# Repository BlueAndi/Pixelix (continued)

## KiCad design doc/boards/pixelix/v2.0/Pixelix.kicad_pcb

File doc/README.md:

# PIXELIX <!-- omit in toc -->

## Documentation  <!-- omit in toc -->

- [Hardware](#hardware)
- [Software](#software)
- [Issues, Ideas And Bugs](#issues-ideas-and-bugs)
- [License](#license)
- [Contribution](#contribution)

## Hardware

- [Boards](./boards/README.md)
- [Sensors](SENSORS.md)

## Software

- [Software architecture](./architecture/README.md)
- [CI and release workflows](WORKFLOWS.md)
- [Software configuration management](./config/README.md)
  - [Toolchain installation](./config/TOOLCHAIN-INSTALLATION.md)
  - [Software build](./config/SW-BUILD.md)
  - [Software update](./config/SW-UPDATE.md)
- [Plugins](PLUGINS.md)
- [Plugin Development](PLUGIN-DEV.md)
- [Websocket API description](WEBSOCKET.md)
- [Coredump Analysis & Debugging](COREDUMP-ANALYSIS.md)
- [Alternative icons](ICONS.md)
- [Configuration examples for GrabViaMqttPlugin and GrabViaRestPlugin.](./grabConfigs/README.md)

## Issues, Ideas And Bugs

If you have ideas or found a bug, create an [issue](https://github.com/BlueAndi/Pixelix/issues). If you want to fix it yourself, clone the repository and open a pull request.

## License

The whole source code is published under the [MIT license](http://choosealicense.com/licenses/mit/).
Consider the different licenses of the used third party libraries too!

## Contribution

Unless you explicitly state otherwise, any contribution intentionally submitted for inclusion in the work by you, shall be licensed as above, without any
additional terms or conditions.

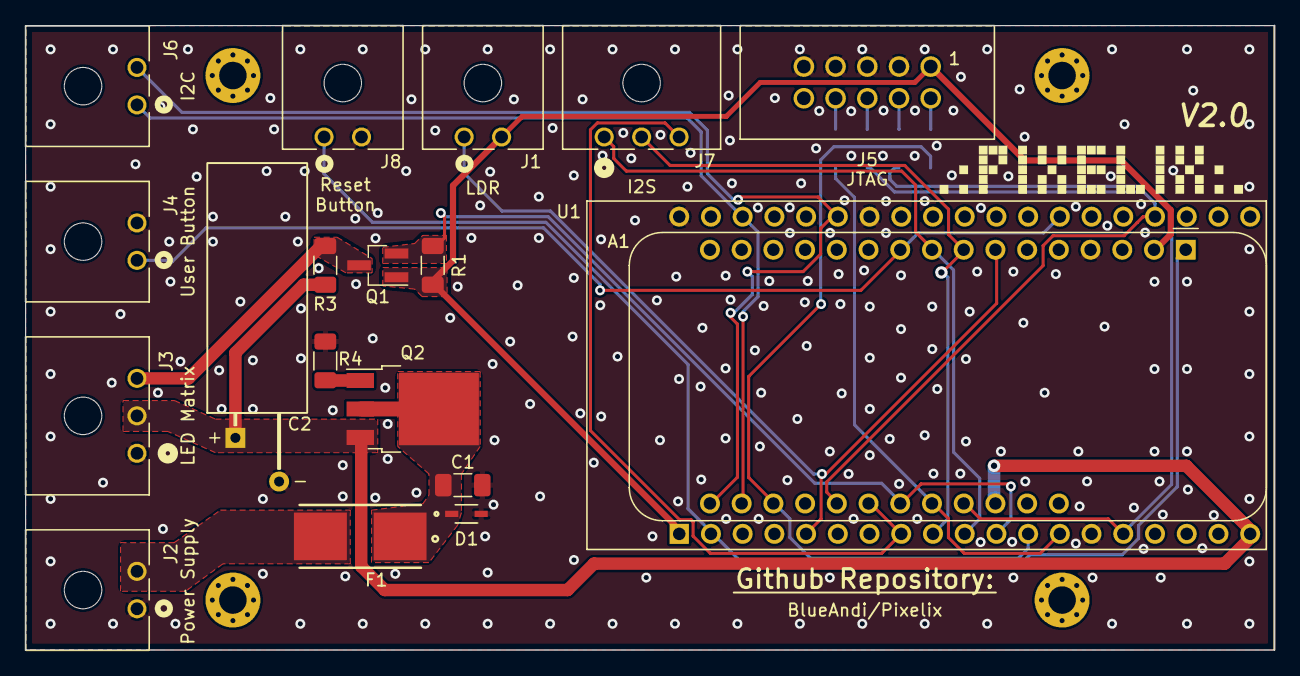
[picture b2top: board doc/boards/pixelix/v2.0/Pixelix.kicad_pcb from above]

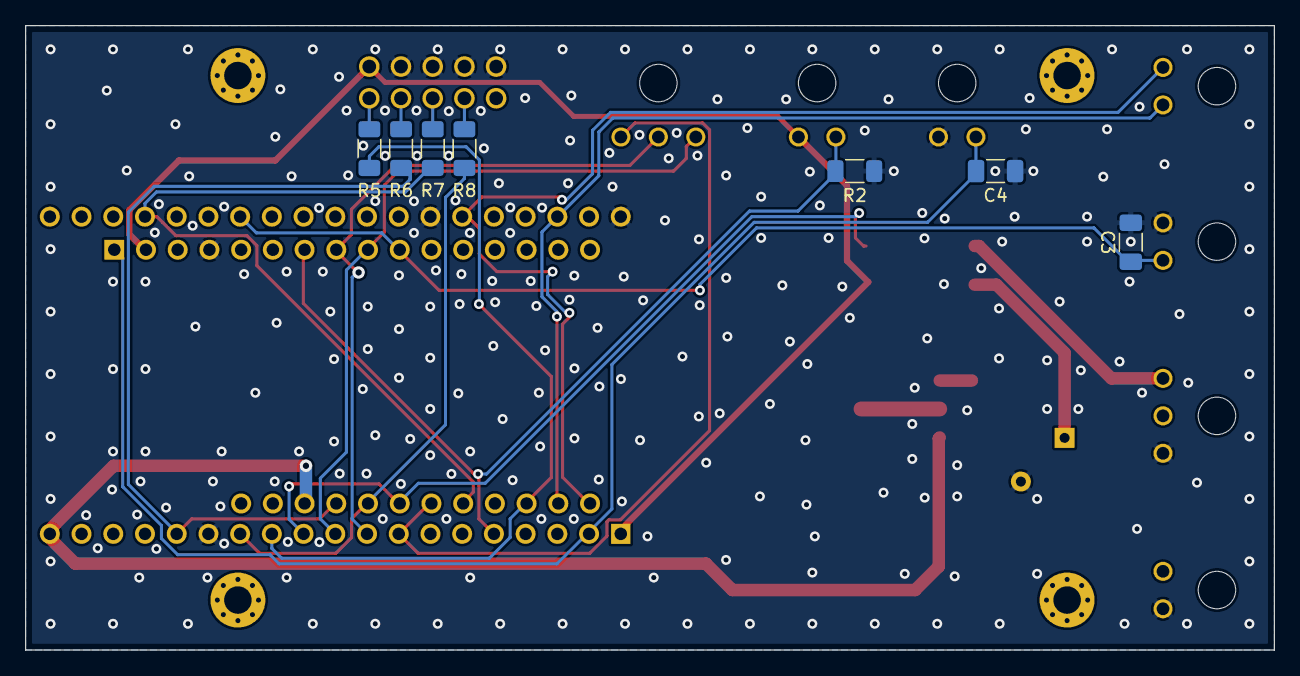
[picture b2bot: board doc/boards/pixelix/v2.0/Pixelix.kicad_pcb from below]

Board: 2 copper layers, 100.0 x 50.0 mm, 30 parts (7 on the bottom side), 24 nets.

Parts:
A1: Adafruit_Feather_V2_ESP32
C1, C3, C4: 100n; C_1206_3216Metric_Pad1.33x1.80mm_HandSolder
C2: 1000u / 16V; CP_Radial_D8.0mm_P3.50mm_horizontal
D1: CDSOD323-T05C
F1: 4A; FUSE_0154004.DR
H1, H2, H3, H4: MountingHole_Pad; MountingHole_2.2mm_M2_Pad_Via
J1, J2, J4, J6, J8: Conn_01x02; 66200211022
J3, J7: Conn_01x03; 66200311022
J5: Conn_02x05_Odd_Even; 61201021621
Q1: NMOS_GSD_BSS138; SOT-23_Handsoldering
Q2: PMOS_GDS_STD26P3LLH6; TO-252-3_TabPin2
R1: 10k; R_1206_3216Metric_Pad1.30x1.75mm_HandSolder
R2: 1k; R_1206_3216Metric_Pad1.30x1.75mm_HandSolder
R3: 1.2k; R_1206_3216Metric_Pad1.30x1.75mm_HandSolder
R4: 100k; R_1206_3216Metric_Pad1.30x1.75mm_HandSolder
R5, R6, R7, R8: 100; R_1206_3216Metric_Pad1.30x1.75mm_HandSolder
U1: ESP32-DEVKITC-32D; MODULE_ESP32-DEVKITC-32D

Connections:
+3V3: A1.2 (3V3), J1.2, J5.1, Q1.1 (G), R1.1, U1.1 (3V3)
/HV-DATA-OUT: J3.3, Q1.3 (D), R3.2
/I2S_CLK: A1.9 (IO36/A4), J7.1, U1.10 (IO26)
/I2S_Data_IN: A1.22 (A9/IO33), J7.3, U1.8 (IO33)
/I2S_WS: A1.8 (I39/A3), J7.2, U1.9 (IO25)
/LDR-ANALOG-IN: A1.7 (I34/A2), J1.1, R2.1, U1.5 (IO34)
/LV-DATA-OUT: A1.23 (A10/IO27), Q1.2 (S), R1.2, U1.11 (IO27)
/MTCK: A1.25 (A12/IO13), R6.2, U1.15 (IO13)
/MTDI: A1.24 (A11/IO12), R8.2, U1.13 (IO12)
/MTDO: A1.21 (A8/IO15), R7.2, U1.35 (IO15)
/MTMS: A1.19 (A6/IO14), R5.2, U1.12 (IO14)
/RESET: A1.1 (~RESET), C4.1, J8.1, U1.2 (EN)
/SCL: A1.18 (SCL/IO22), J6.1, U1.22 (IO22)
/SDA: A1.17 (SDA/IO23), J6.2, U1.25 (IO21)
/USER-BUTTON: A1.10 (IO4/A5), C3.1, J4.1, U1.32 (IO4)
/VCC-PROTECTED: A1.26 (USB), C2.1, J3.2, Q2.3 (S), R3.1, U1.19 (EXT_5V)
GND: A1.4 (GND), C1.2, C2.2, C3.2, C4.2, D1.2, J2.1, J3.1, J4.2, J5.3, J5.5, J5.7, J5.9, J8.2, R2.2, R4.2, U1.14 (GND1), U1.20 (GND3), U1.26 (GND2)
unnamed: C1.1, D1.1, F1.1, Q2.2 (D)
unnamed: F1.2, J2.2
unnamed: J5.2, R5.1
unnamed: J5.4, R6.1
unnamed: J5.6, R7.1
unnamed: J5.8, R8.1
unnamed: Q2.1 (G), R4.1

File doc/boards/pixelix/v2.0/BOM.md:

# PIXELIX
![PIXELIX](../../../images/LogoBlack.png)

[![License](https://img.shields.io/badge/license-MIT-blue.svg)](http://c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

# BOM

| Amount | Description | Package | Part | URL |
| --- | --- | --- | --- | --- |
| 1 | Adafruit Feather V2 | Feather V2 | A1 | [Adafruit](https://www.adafruit.com/product/5400), [Amazon](https://www.amazon.de/-/en/Adafruit-ESP32-Feather-V2-8MB-Fla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, [Mouser](https://www.mouser.de/ProductDetail/Adafruit/5400?qs=MyNHzdo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 |
| 3 | Capacitor 100 nF | C1206 | C1, C3, C4 | [Reichelt](https://www.reichelt.de/vielschicht-kerko-100nf-50v-125-c-ke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, [Mouser](https://www.mouser.de/ProductDetail/KEMET/C1206C104K5RACTM?q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 |
| 1 | Capacitor 1000 uF / 16 V | E5-8.5 | C2 | [Reichelt](https://www.reichelt.de/elko-radial-1-0-mf-16-v-105-c-low-es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, [Mouser](https://www.mouser.de/ProductDetail/Panasonic/EEU-FR1C102L?q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 |
| 4 | Resistor 100 Ohm | R1206 | R5, R6, R7, R8 | [Reichelt](https://www.reichelt.de/smd-widerstand-1206-100-ohm-250-mw-5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, [Mouser](https://www.mouser.de/ProductDetail/YAGEO/RC1206JR-07100RL?q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 |
| 1 | Resistor 1 kOhm | R1206 | R2 | [Reichelt](https://www.reichelt.de/smd-widerstand-1206-1-0-kohm-250-mw-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, [Mouser](https://www.mouser.de/ProductDetail/YAGEO/RC1206JR-071KL?qs=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  |
| 1 | Resistor 1.2 kOhm | R1206 | R3 | [Reichelt](https://www.reichelt.de/smd-widerstand-1206-1-2-kohm-250-mw-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, [Mouser](https://www.mouser.de/ProductDetail/YAGEO/RC1206JR-071K2L?qs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  |
| 1 | Resistor 10 kOhm | R1206 | R1 | [Reichelt](https://www.reichelt.de/smd-widerstand-1206-10-kohm-250-mw-5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, [Mouser](https://www.mouser.de/ProductDetail/YAGEO/RC1206JR-0710KL?qs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 |
| 1 | Resistor 100 kOhm | R1206 | R4 | [Reichelt](https://www.reichelt.de/smd-widerstand-1206-100-kohm-250-mw-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, [Mouser](https://www.mouser.de/ProductDetail/YAGEO/RC1206FR-07100KL?q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 |
| 1 | ESD suppressor CDSOD323-T05C | SOD-323 | D1 | [Conrad](https://www.conrad.de/de/p/bourns-tvs-diode-cdsod323-t05c-so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, [Farnell](https://de.farnell.com/bourns/cdsod323-t05c/tvs-diode-bidir-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, [Mouser](https://www.mouser.de/ProductDetail/Bourns/CDSOD323-T05C?qs=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 |
| 1 | Micro fuse block, 4A slow | OMNI-BLOK | F1 | [Reichelt](https://www.reichelt.de/smd-sicherungshalter-mit-sicherung-4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, [Farnell](https://de.farnell.com/littelfuse/0154004-drt/sicherung-smd-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, [Mouser](https://www.mouser.de/ProductDetail/?qs=gu7KAQ731UQeedYeniUN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 |
| 1 | Espressif ESP32-DEVKIT | ESP32-DEVKITC-32D | U1 | [Mouser](https://www.mouser.de/ProductDetail/Espressif-Systems/ESP32-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, [Amazon](https://www.amazon.de/s?k=ESP32-DEVKITC-32D&i=computers&__mk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 |
| 1 | N-channel mosfet BSS138 | SOT23 | Q1 | [Reichelt](https://www.reichelt.de/mosfet-n-ch-50v-0-22a-0-36w-sot-23-b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, [Farnell](https://de.farnell.com/on-semiconductor/bss138/mosfet-n-kana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, [Mouser](https://www.mouser.de/ProductDetail/onsemi-Fairchild/BSS138?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 |
| 1 | P-channel mosfet STD26P3LLH6 | TO252 | Q2 | [Reichelt](https://www.reichelt.de/mosfet-p-ch-30v-12a-0-03r-to252-std2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, [Farnell](https://de.farnell.com/stmicroelectronics/std26p3llh6/mosfet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, [Mouser](https://www.mouser.de/ProductDetail/STMicroelectronics/STD26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 |
| 5 | Conn_01x02 | Wuerth Elektronik 66200211022 | J1, J2, J4, J6, J8 | [Farnell](https://de.farnell.com/wurth-elektronik/66200211022/steckv-s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, [Mouser](https://www.mouser.de/c/?q=66200211022) |
| 2 | Conn_01x03 | Wuerth Elektronik 66200311022 | J3, J7 | [Farnell](https://de.farnell.com/wurth-elektronik/66200311022/stiftlei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, [Mouser](https://www.mouser.de/ProductDetail/Wurth-Elektronik/6620031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 |
| 1 | Conn_02x05_Odd_Even | Wuerth Elektronik 61201021621 | J5 | [Farnell](https://de.farnell.com/wurth-elektronik/61201021621/stiftlei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, [Mouser](https://www.mouser.de/ProductDetail/Wurth-Elektronik/6120102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 |
| --- | --- | --- | --- | --- |
| 5 | Plug_01x02 | Wuerth Elektronik 662002013322 | J1*, J2*, J4*, J6*, J8* | [Mouser](https://www.mouser.de/ProductDetail/Wurth-Elektronik/6620020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 |
| 2 | Plug_01x03 | Wuerth Elektronik 662003013322 | J3*, J7* | [Mouser](https://www.mouser.de/ProductDetail/Wurth-Elektronik/6620030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 |
| 1 | WS2812B 5050 8x32 RGB Flexible LED Panel Matrix | - | - | [Amazon](https://www.amazon.de/CHINLY-Flexible-Individuellement-adres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 |
| 1 | Power supply 5 V / 5 A (4 A would be enough) | - | - | [Reichelt](https://www.reichelt.de/tischnetzteil-25-w-5-v-5-a-mw-gst40a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, [Mouser](https://www.mouser.de/ProductDetail/CUI-Inc/SDM36-5-U-P5?qs=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 |
| 1 | Power cable | - | - | [Reichelt](https://www.reichelt.de/netzkabel-schutzkontaktstecker-gew-1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, [Mouser](https://www.mouser.de/ProductDetail/Qualtek/364002-D01?qs=HF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 |
| 1 | Power supply plug | - | - | [Mouser](https://www.mouser.de/ProductDetail/CUI-Devices/PJ-065A?qs=W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 |
| 1 | USER-Button | - | - | [Amazon](https://www.amazon.de/-/en/gp/product/B08L49F7DV) |
| 1 | RESET-Button | - | - | [Amazon](https://www.amazon.de/-/en/gp/product/B08YMZGLWX) |
| 1 | Light Sensor  | LDR5528  | - | [Amazon](https://www.amazon.de/-/en/AZDelivery-pieces-resistor-diodes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 |
| 1 | Audio Sensor-Module | INMP441  | - | [Amazon](https://www.amazon.de/-/en/gp/product/B09JFDJ9BF) |
| 4 | Insert-Nuts M2 | - | - | [Amazon](https://www.amazon.de/ruthex-Gewindeeinsatz-St%C3%BCck-Gewin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

* Note, only **ONE** ESP32 is required. Either U1 or A1.
* Note, you can also use the *Molex 2157601002* connectors for J1, J2, J4, J6 and J8 and the *Molex 2157601003* for J3 and J7.
* Note, you can also use the *Molex 2157591002* plugs for J1*, J2*, J4*, J6* and J8* and the *Molex 2157591003* for J3* and J7*. You also need crimp terminals (e.g. *Wuerth Elektronik 66200113722DEC* or *Molex 2064600021*)
* Do **NOT** combine connectors and plugs from Molex and Wuerth Elektronik!

# Issues, Ideas And Bugs
If you have further ideas or you found some bugs, great! Create a [issue](https://github.com/BlueAndi/esp-rgb-led-matrix/issues) or if you are able and willing to fix it by yourself, clone the repository and create a pull request.

# License
The whole source code is published under the [MIT license](http://choosealicense.com/licenses/mit/).

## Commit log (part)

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2026-06-03 Parse URL params into JSON and pass to plugins for advanced web config (ChicagoBusTrackerPlugin)
2026-06-08 Use proper formatting
2026-06-08 Make getApiKey private and const
2026-06-08 Fixup ChicagoBusTracker doxygen comments
2026-06-08 Explicit else cases in ChicagoBusTrackerPlugin::getTopic
2026-06-08 Refactor ChicagoBusTrackerPlugin::getApiKey to use JsonFile
2026-06-08 Explicit operator precedence in ChicagoBusTracker comparisons
2026-06-09 Bugfix: m_scrollCtrl is updated by paint() method, but not m_scrollCtrlNew. This results in a infinite loop in SysMsgPlugin in case it requires the scroll information.
2026-06-09 Bugfix: If a slot is sticky that not contains the SysMsgPlugin, a system message won't be shown. Now the sticky flag will be removed in this case.
2026-06-09 Make ChicagoBusTrackerPlugin::getRoutes,getDirections,getStops const
2026-06-09 Enable ChicagoBusTrackerPlugin in "normal" config
2026-06-10 Ensure that the welcome message is shown in every situation and as long as the plugin with the alias "_welcome" exists.
2026-06-10 Bugfix: Block stale scroll info during fade-out transition and scrolling always once more than specified
2026-06-13 The memory monitor didn't print the largest memory block with the same capabilities than the failed allocation. Thats fixed now.
2026-06-13 The source map files are used for debugging and do not contain any sensitive information. They are not needed for the normal operation of the web interface and can be excluded from caching to save me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
2026-06-13 ESPAsyncWebServer updated to v3.11.1
2026-06-14 Minimize memory usage for ChicagoBusTracker REST requests
2026-06-14 More aggressive memory savings in ChicagoBusTracker
2026-06-14 Separate route number text from route info text in ChicagoBusTrackerPlugin
2026-06-15 Reserve string memory to avoid multiple reallocations.
2026-06-15 reserve() method added to native Arduino wrapper.
2026-06-16 The GifImgPlayer uses for disposal method 3 (restore to previous) the background color because of resource constraints. Problem: The current implementation doesn't respect if global color table is av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
2026-06-17 Refactor ChicagoBusTrackerView
2026-06-17 Add 32x16 layout to ChicagoBusTrackerPlugin
2026-06-18 Use PSRAM for JSON documents if available.
2026-06-18 RestService and plugins are using PsramJsonDocument to use PSRAM as much as possible.
2026-06-20 Fix typos in ChicagoBusTracker 32x16
2026-06-20 Add 64x64 view for ChicagoBusTracker
2026-06-20 Add ChicagoBusTracker API documentation
2026-06-20 Minimize ChicagoBusTracker string reallocations
2026-06-20 Fix bugs in ChciagoBusTrackerPlugin Web UI
2026-06-20 Switch ChicagoBusTracker to show up to 3 arrivals
2026-06-20 Update ChicaagoBusTracker to 1-min update intervals thanks to higher API limits
2026-06-21 Recommended VSCode extensions updated.
2026-06-21 Fix ChicagoBusTracker OpenAPI spec
2026-06-21 ChicagoBusTracker PR feedback cleanup
2026-06-22 Replace ChicagoBusTracker String allocations with const char*
2026-06-22 Fix extraneous string declaration in ChicagoBusTrackerViewGeneric
2026-06-22 Add link to sign up for a CTA Bus Tracker API Key
2026-06-22 Remove unnecessary ChicagoBusTracker shared API key file
